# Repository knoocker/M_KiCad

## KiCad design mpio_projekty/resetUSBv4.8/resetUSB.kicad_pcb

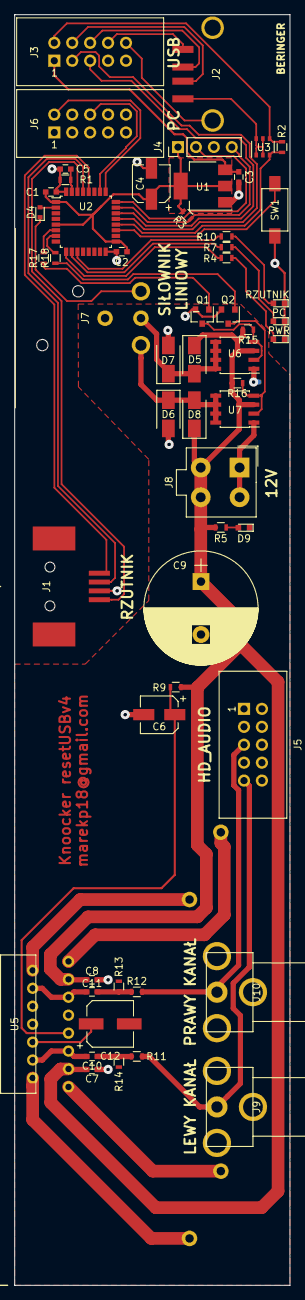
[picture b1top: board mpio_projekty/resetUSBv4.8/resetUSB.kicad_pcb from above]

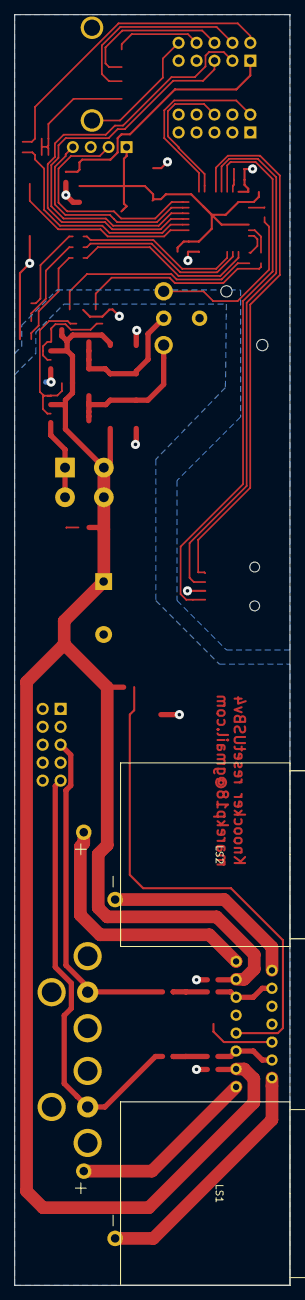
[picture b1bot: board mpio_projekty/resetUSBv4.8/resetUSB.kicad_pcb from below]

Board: 2 copper layers, 39.0 x 180.0 mm, 58 parts (2 on the bottom side), 52 nets.

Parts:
C1, C2, C3, C5, C7, C8: 100n; C_0603
C4, C6: 10u; CP_Elec_5x5.3
C9: 4700u; CP_Radial_D16.0mm_P7.50mm
C10, C11: 0.47u; C_0603
C12: 47u; CP_Elec_6.3x5.3
D1, D9: RED; LED_0603
D2: GREEN; LED_0603
D3: BLUE; LED_0603
D4: 1PS79SB70; D_SOD-523
D5, D6, D7, D8: US1D; D_SMA
J1: USBB-G-SMD; USB-B_SMD
J2: TUEA4F2SOBHT; USB-A_SMD
J3, J5, J6: Conn_02x05; IDC10
J4: SWD_4pin; Pin_Header_Straight_1x04_Pitch2.54mm
J7: AC3MAH-AU-PRE
J8: Mini-Fit Jr; 4,2mm; Molex_MiniFit-JR-5556-04A_2x02x4.20mm_Straight
J9, J10: FC68391
LS1, LS2: NLJ2MD-H
Q1, Q2: BC817; SOT-23
R1, R2, R3, R5: 100K; R_0603
R4: 22K; R_0603
R7: 6K8; R_0603
R9: 47K; R_0603
R10: 33K; R_0603
R11, R12: 4K7; R_0603
R13, R14, R15, R16, R17, R18: 10K; R_0603
SW1: TACTM-34N-F; SW_3x6_1,6x7,4
U1: LD1117S33TR; SOT-223-3_TabPin2
U2: STM32F042K6Tx; LQFP-32_7x7mm_Pitch0.8mm
U3: IRLTS2242; TSOP-6_1.65x3.05mm_Pitch0.95mm
U5: TDA7375; MULTIWATT15
U6, U7: AO4616; SOIC-8_3.9x4.9mm_Pitch1.27mm

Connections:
+3V3: C1.1, C2.1, C4.1, J4.1, R3.2, U1.2, U2.1, U2.5, U2.17
+5V: C3.1, J3.1, U1.3
+12V: C7.1, C8.1, C9.1, D5.1, D6.1, J8.3, J8.4, R5.1, R9.1, R15.2, R16.2, U5.3, U5.13, U6.3, U7.3
/LED_BLUE: R10.2, U2.11
/LED_GREEN: R7.2, U2.10
/LED_RED: R4.2, U2.9
/M_IMP: D4.2, U2.2
/M_IN1: R17.2, U2.6
/M_IN2: R18.2, U2.7
/OUT2_L: J5.9, J9.1, R11.1
/OUT2_R: J5.5, J10.1, R12.1
/PC_LED: J6.2, U2.25
/PC_PWR: J6.6, U2.26
/PRZYCISK: SW1.2, U2.19
/RZUTNIK_DM: J1.2, U2.29
/RZUTNIK_DP: J1.3, U2.28
/RZUTNIK_VBUS: J1.1, U2.30
/SWCLK: J4.2, U2.24
/SWDIO: J4.4, R3.1, U2.23
/USB_M: J3.3, U2.21
/USB_P: J3.5, U2.22
/USB_PWR: R2.2, U2.20, U3.3
GND: C1.2, C2.2, C3.2, C4.2, C5.2, D1.1, D2.1, D3.1, J1.4, J1.5, J3.7, J4.3, R1.1, SW1.1, U1.1, U2.16, U2.32
GNDA: C6.2, C7.2, C8.2, C9.2, C12.2, D7.2, D8.2, D9.1, J5.2, J8.1, J8.2, J9.2, J10.2, Q1.2, Q2.2, R13.2, R14.2, U5.8, U5.9, U6.1, U7.1
unnamed: C5.1, R1.2, U2.31
unnamed: C6.1, R9.2, U5.7
unnamed: C10.1, R11.2, R14.1
unnamed: C10.2, U5.4, U5.5
unnamed: C11.1, R12.2, R13.1
unnamed: C11.2, U5.11, U5.12
unnamed: C12.1, U5.6
unnamed: D1.2, R4.1
unnamed: D2.2, R7.1
unnamed: D3.2, R10.1
unnamed: D4.1, J7.1
unnamed: D5.2, D7.1, J7.3, U6.5, U6.6, U6.7, U6.8
unnamed: D6.2, D8.1, J7.2, U7.5, U7.6, U7.7, U7.8
unnamed: D9.2, R5.2
unnamed: J2.1, U3.1, U3.2, U3.5, U3.6
unnamed: J2.2, J3.4
unnamed: J2.3, J3.6
unnamed: J2.4, J3.8
unnamed: J2.5, J3.10
unnamed: J3.2, R2.1, U3.4
unnamed: LS1.1, U5.1
unnamed: LS1.2, U5.2
unnamed: LS2.1, U5.15
unnamed: LS2.2, U5.14
unnamed: Q1.1, R17.1
unnamed: Q1.3, R15.1, U6.2, U6.4
unnamed: Q2.1, R18.1
unnamed: Q2.3, R16.1, U7.2, U7.4

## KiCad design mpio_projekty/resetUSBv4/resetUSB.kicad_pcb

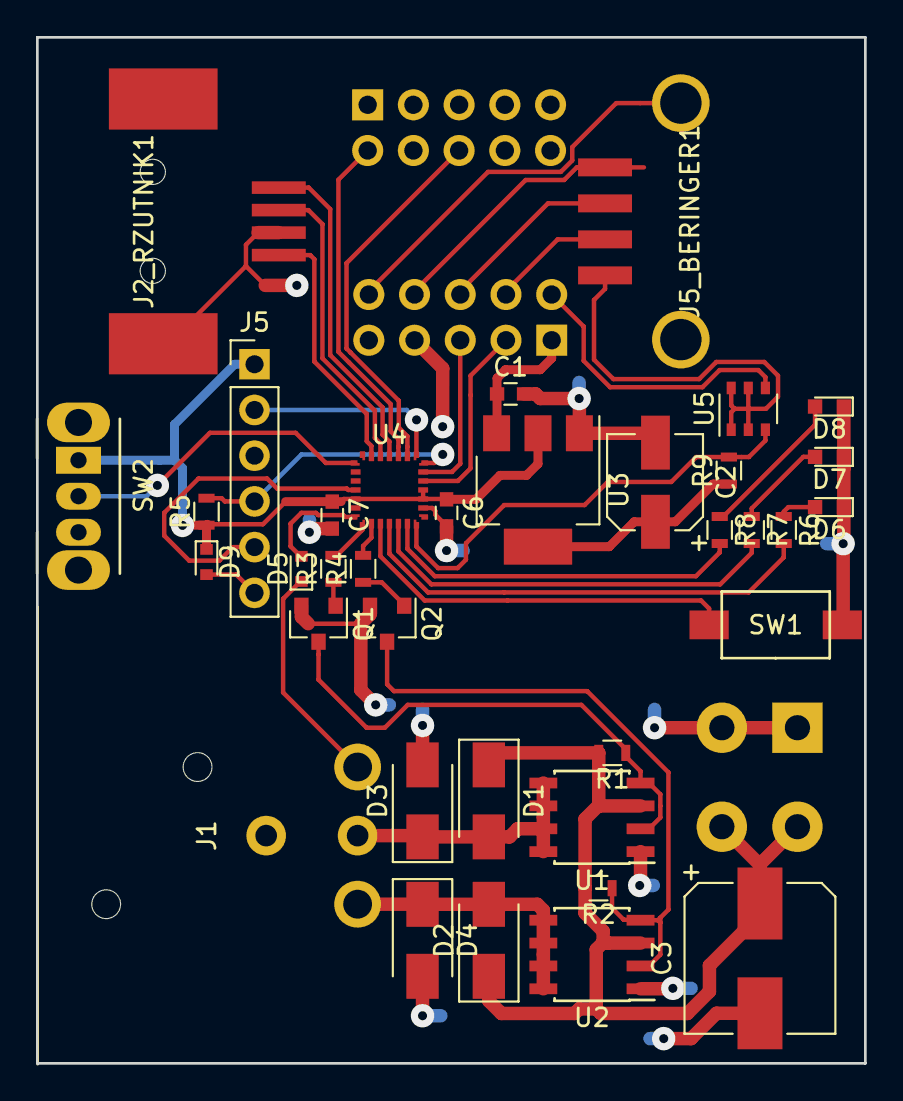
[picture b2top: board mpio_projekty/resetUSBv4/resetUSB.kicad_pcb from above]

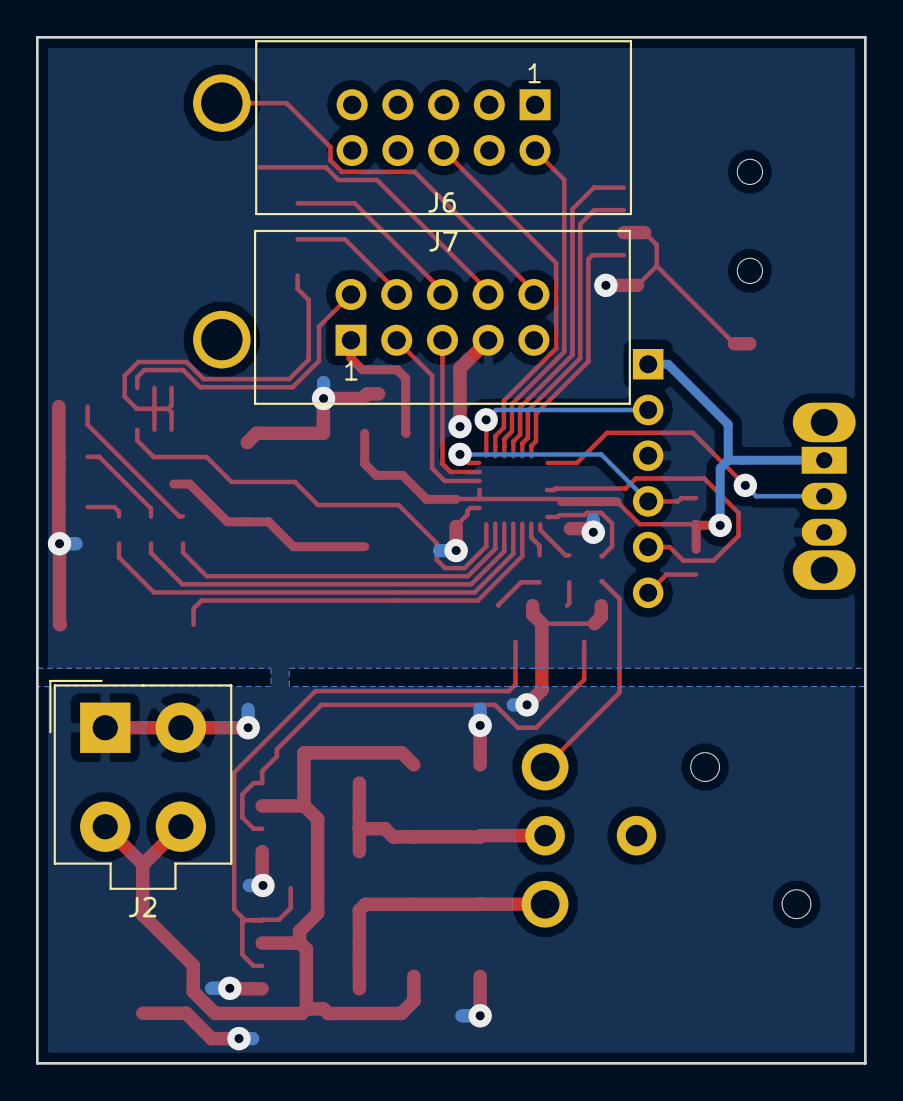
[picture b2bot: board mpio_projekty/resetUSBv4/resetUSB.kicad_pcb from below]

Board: 2 copper layers, 46.0 x 57.0 mm, 39 parts (3 on the bottom side), 40 nets.

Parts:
C1, C6, C7: 100n; C_0603
C2: 10u; CP_Elec_5x5.3
C3: 220uF; CP_Elec_8x10
D1, D2, D3, D4: D; D_SMA
D5: D_Schottky; D_SOD-523
D6: RED; LED_0603
D7: GREEN; LED_0603
D8: BLUE; LED_0603
D9: D_Schott; D_SOD-523
J1: XLR3; AC3MAH-AU-PRE
J2: Mini-Fit Jr; 4,2mm; Molex_MiniFit-JR-5556-04A_2x02x4.20mm_Straight
J2_RZUTNIK1: DS1098-BN0; USB-B_SMD
J5: SWD_6pin; Pin_Header_Straight_1x06_Pitch2.54mm
J5_BERINGER1: DS1098-BN0; USB-A_SMD
J6, J7: Conn_02x05; IDC10
Q1, Q2: BC817; SOT-23
R1, R2, R3, R4: 10K; R_0603
R5, R9: 100K; R_0603
R6: 22K; R_0603
R7: 6K8; R_0603
R8: 33K; R_0603
SW1: TACTM-34N-F; SW_3x6_1,6x7,4
SW2: SW_SPDT; SW_CuK_OS102011MA1QN1_SPDT_Angled
U1, U2: AO4616; SOIC-8_3.9x4.9mm_Pitch1.27mm
U3: LD1117S33TR; SOT-223-3_TabPin2
U4: STM32F042G4Ux; UFQFPN28_4x4mm_Pitch0.5mm
U5: IRLTS2242; TSOP-6_1.65x3.05mm_Pitch0.95mm

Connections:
+3V3: C2.1, C6.1, C7.1, D9.1, J5.1, R5.1, R9.1, SW2.1, U3.2, U4.5, U4.17, U4.18
+5V: C1.1, J6.1, U3.3
+12V: C3.1, D1.1, D2.1, J2.3, J2.4, R1.2, R2.2, U1.3, U2.3
/LED_PC: R7.2, U4.12
/LED_PWR: R6.2, U4.11
/LED_RZUTNIK: R8.2, U4.13
/M_IMP: D5.2, U4.7
/M_IN1: R3.2, U4.8
/M_IN2: R4.2, U4.9
/PC_LED+: J7.2, U4.24
/PC_PWR: J7.6, U4.23
/RZUTNIK_D+: J2_RZUTNIK1.3, U4.25
/RZUTNIK_D-: J2_RZUTNIK1.2, U4.26
/RZUTNIK_VBUS: J2_RZUTNIK1.1, U4.27
/SERWISOWY: SW1.2, U4.10
/SWCLK: J5.2, U4.22
/SWDIO: J5.4, R5.2, U4.21
/USB_M: J6.3, U4.19
/USB_P: J6.5, U4.20
/USB_PWR: R9.2, U4.14, U5.3
/nRST: J5.5, U4.4
GND: C1.2, C2.2, C3.2, C6.2, C7.2, D3.2, D4.2, D6.1, D7.1, D8.1, J2.1, J2.2, J2_RZUTNIK1.4, J2_RZUTNIK1.5, J5.3, J6.7, Q1.2, Q2.2, SW1.1, SW2.3, U1.1, U2.1, U3.1, U4.16
unnamed: D1.2, D3.1, J1.3, U1.5, U1.6, U1.7, U1.8
unnamed: D2.2, D4.1, J1.2, U2.5, U2.6, U2.7, U2.8
unnamed: D5.1, J1.1
unnamed: D6.2, R6.1
unnamed: D7.2, R7.1
unnamed: D8.2, R8.1
unnamed: D9.2, J5.6
unnamed: J5_BERINGER1.1, U5.1, U5.2, U5.5, U5.6
unnamed: J5_BERINGER1.2, J6.4
unnamed: J5_BERINGER1.3, J6.6
unnamed: J5_BERINGER1.4, J6.8
unnamed: J5_BERINGER1.5, J6.10
unnamed: J6.2, U5.4
unnamed: Q1.1, R3.1
unnamed: Q1.3, R1.1, U1.2, U1.4
unnamed: Q2.1, R4.1
unnamed: Q2.3, R2.1, U2.2, U2.4
unnamed: SW2.2, U4.1
